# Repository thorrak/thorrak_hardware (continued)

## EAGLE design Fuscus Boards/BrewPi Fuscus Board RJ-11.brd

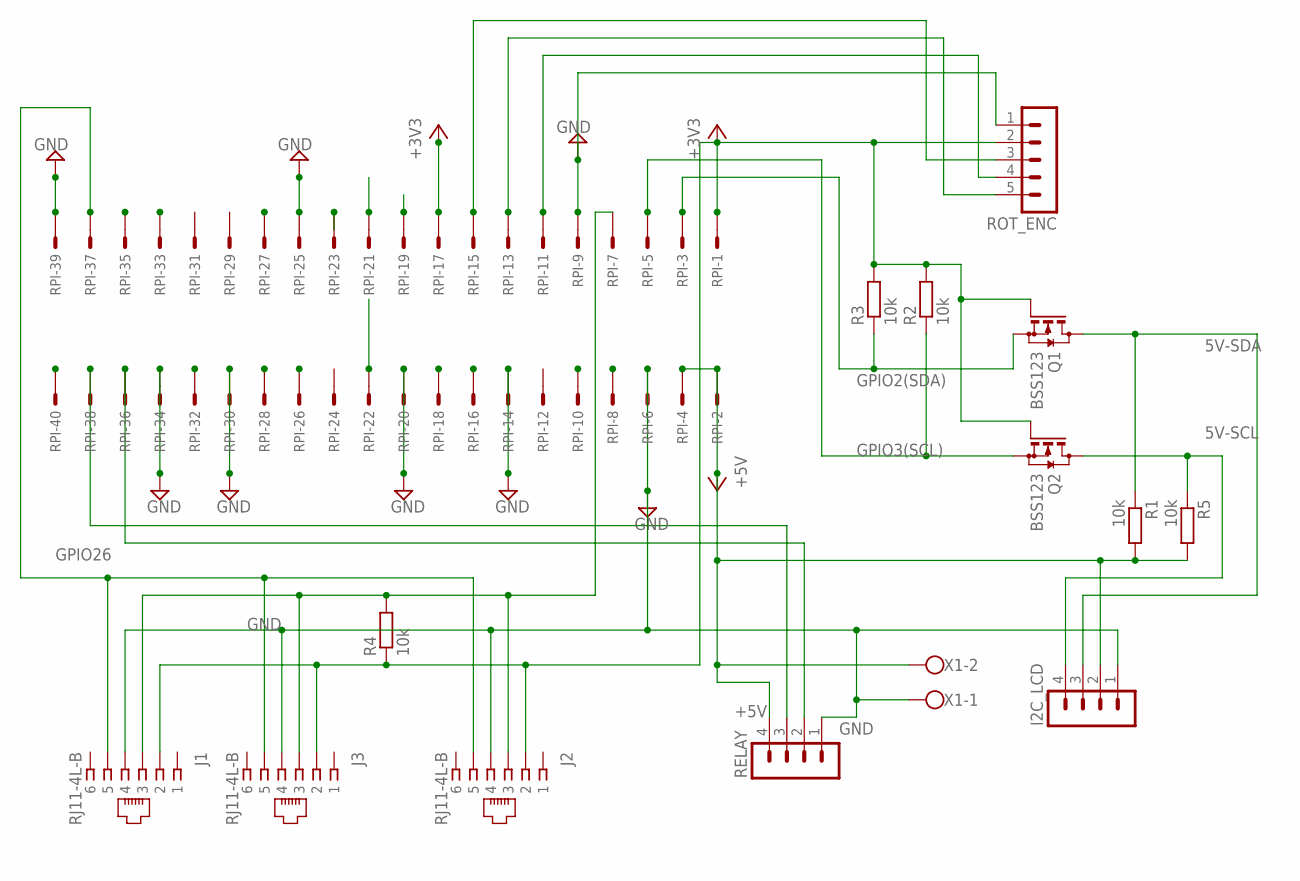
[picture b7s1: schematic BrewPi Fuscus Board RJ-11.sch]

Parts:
I2C_LCD: MA04-1
J1, J2, J3: RJ11-4L-B; RJ11-NO_SHIELD
Q1, Q2: BSS123; SOT23
R1, R2, R3, R4, R5: 10k; M1206
RELAY: MA04-1
ROT_ENC: MA05-1
RPI: 057-040-1
X1: W237-102

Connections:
5V-SCL: I2C_LCD.4, Q2.3 (D), R5.1
5V-SDA: I2C_LCD.3, Q1.3 (D), R1.1
+3V3: J1.2, J2.2, J3.2, Q1.1 (G), Q2.1 (G), R2.2, R3.2, R4.1, ROT_ENC.2, RPI.1, RPI.17
+5V: I2C_LCD.2, R1.2, R5.2, RELAY.4, RPI.2, RPI.4, X1.2
GND: I2C_LCD.1, J1.4, J2.4, J3.4, RELAY.1, ROT_ENC.1, RPI.6, RPI.9, RPI.14, RPI.20, RPI.25, RPI.30, RPI.34, RPI.39, X1.1
GPIO2(SDA): Q1.2 (S), R3.1, RPI.3
GPIO3(SCL): Q2.2 (S), R2.1, RPI.5
GPIO7(SPI_CE1_N): RPI.26
GPIO9(SPI_MISO): RPI.21
GPIO10(SPI_MOSI): RPI.19
GPIO11(SPI_SCLK): RPI.23
GPIO12: RPI.32
GPIO13: RPI.33
GPIO14(TXD0): RPI.8
GPIO15(RXD0): RPI.10
GPIO16: RELAY.2, RPI.36
GPIO17(GPIO_GEN0): ROT_ENC.4, RPI.11
GPIO19: RPI.35
GPIO20: RELAY.3, RPI.38
GPIO21: RPI.40
GPIO22(GPIO_GEN3): ROT_ENC.3, RPI.15
GPIO23(GPIO_GEN4): RPI.16
GPIO24(GPIO_GEN5): RPI.18
GPIO26: J1.5, J2.5, J3.5, RPI.37
GPIO27(GPIO_GEN2): ROT_ENC.5, RPI.13
ID_SC: RPI.28
ID_SD: RPI.27
unnamed: J1.3, J2.3, J3.3, R4.2, RPI.7
RST: RPI.22

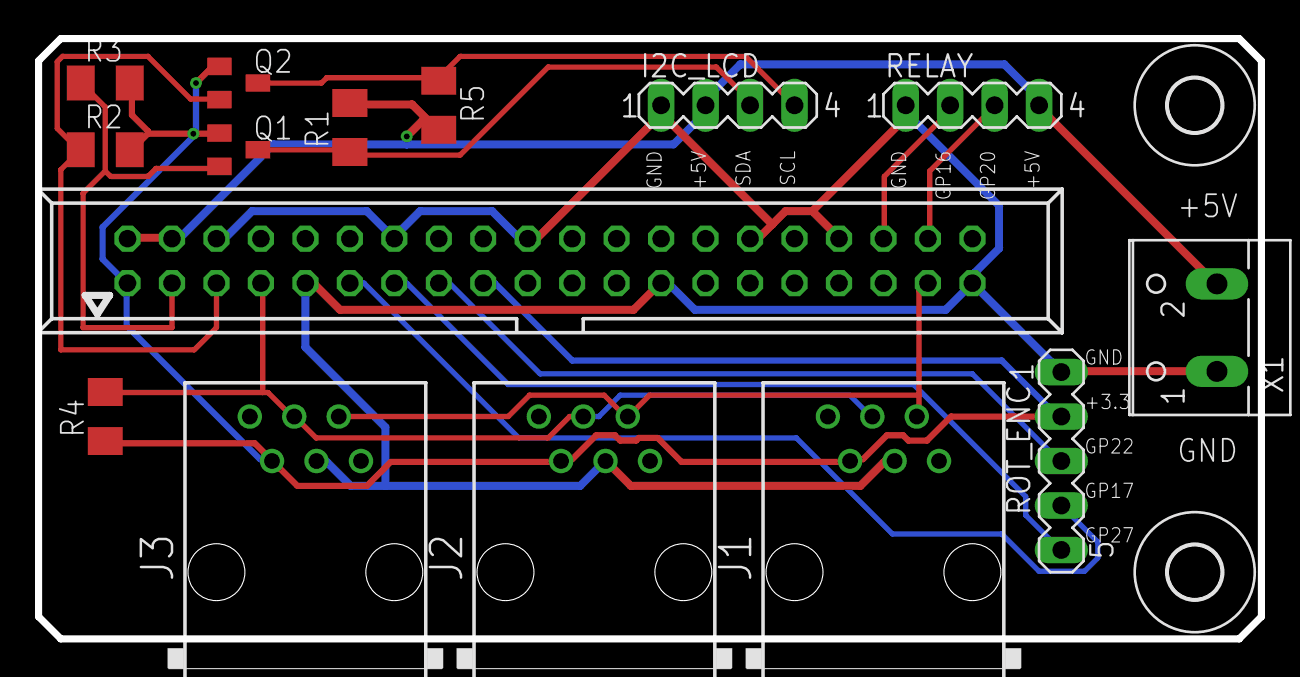
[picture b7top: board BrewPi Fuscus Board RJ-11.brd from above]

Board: 2 copper layers, 69.9 x 34.3 mm, 17 parts (0 on the bottom side), 14 nets.

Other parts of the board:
U$3, U$4: 3,0

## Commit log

2019-12-01 Adding boards
2019-12-01 Fix relative links
2019-12-06 Updating to latest
2020-05-31 Add voltage selection to SMD boards
2020-05-31 Add SMD notes & remove links to pcbs.io
2020-05-31 remove ds store
2020-05-31 Bring up to date
2020-05-31 Removing ds_store
2020-05-31 Updating LCD TH Dupont design
2020-05-31 Updating readme
2020-05-31 Updating images
2020-05-31 Updating No LCD Boards
2020-05-31 Update No LCD board
2020-05-31 Updating TH Screw board
2020-05-31 Add common components language
2020-05-31 Update RJ-45 Board Design
2020-06-02 Update sensor breakout boards
2020-06-02 Add project pages
2020-06-02 Add the majority of the main container files
2020-06-02 Finalize main PCB BOM
2020-06-02 Update case lid info
2020-06-03 Adding sensor box info
2020-06-03 Updating board designs and adding DirtyPCB Links
2020-06-05 Update sensor breakout board
2020-06-05 Updating text/links
2020-06-06 Update sensor breakout container
2020-06-06 Update tindie links
2020-06-06 Add Boards
2020-10-06 Add NoRJ PCB
2020-10-06 Fix PCB link
2021-01-01 Adding BrewPi Containers
2021-01-01 Add TiltBridge containers
2021-02-01 Updated TiltBridge containers
2021-02-15 Add TTGO USBC case for TiltBridge
2021-02-15 Update readmes
2021-03-12 Add solder bridge to SMD board design
2022-02-28 Add prusaprinters links
2022-05-07 Update file modes
2022-05-09 Update BoMs and add DigiKey links
2022-06-29 Add controller selection grid
2022-07-11 Add D32 PCBs
2022-07-11 Update ESP32 readme
2023-11-01 Redraw PCB in KiCad 7.0
    Redraw schematic and PCB layout using KiCad 7.0. Add circuit to emulate NTC10k temp sensor.
2023-11-02 Fix footprint for U1
2023-11-10 Add schematic note
2023-12-04 Power to OneWire sensors
    Add trace for power to onewire sensors, adjust silkscreen
2024-12-13 Update project name The BrewPi-ESP8266 project is now known as BrewPi-ESP given the move to reduce support for the ESP8266
2024-12-13 Add RJ-11 and RJ-45 jack breakouts
2024-12-13 Add LoLin D32 v1.1.0 case lid design
2024-12-13 Rename AIO PCB to "OneSize" Renaming the existing AIO PCB as there is a new, true, all-in-one design coming
2024-12-19 Update RJ-45 Sensor Breakout - Updates documentation for board - Adds LCSC part numbers & JLC offsets to design files - Adds JLC BOM/CPL to repo
2024-12-19 Clean up "other" boards
2024-12-20 Add new "BrewPi-ESP Test" Boards These boards take the place of a full BrewPi build for testing new firmware
2024-12-20 Add new "All-in-One" PCBs These PCBs integrate the 2-channel relay board and power supply into a single PCB
2024-12-20 Add case for new "All-in-One" PCBs
2024-12-20 Fix links
2025-03-27 Update Sensor Box designs
2025-03-27 Add updated AIO case design
2025-03-31 Update US Outlet.md
    Adds Tindie link, updates description to describe the PCB better.
2025-03-31 Update AIO US Outlet.md
    Add Tindie link and provisional Bill of Materials
2025-03-31 Update D32 Pro - TFT OneSize.md
    Updates Tindie links and explains discrete components
2025-03-31 Update Single PCB - IRM-10-5.md
    Update Tindie links, pricing, and add note about the case design
2025-03-31 Update Single PCB - PSK-10D-5.md
    Update Tindie link, add note about power supply
2025-04-03 Reorganize Main PCB Container Files
2025-04-03 Add updated main PCB case designs
2025-04-08 Add 3.2in AIO case lid
2025-04-08 Add YouTube Video
2025-04-12 Reorganize
2025-04-16 Add LoLin Bracket STL
